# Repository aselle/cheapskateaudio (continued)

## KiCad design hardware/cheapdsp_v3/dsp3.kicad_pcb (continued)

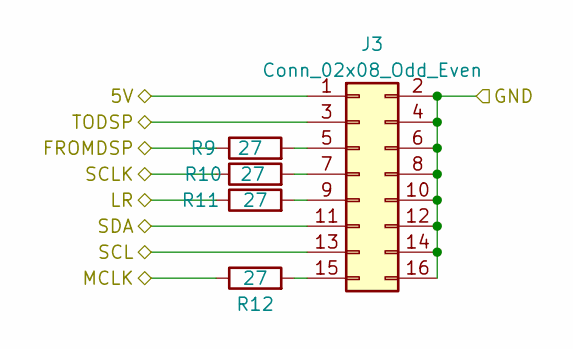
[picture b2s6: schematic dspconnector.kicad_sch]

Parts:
J3: Conn_02x08_Odd_Even; IDC-Header_2x08_P2.54mm_Vertical
R9, R10, R11, R12: 27; R_0603_1608Metric

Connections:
/DSP/I2S2_LR: R11.1; also elsewhere on the board
/DSP/I2S2_SCLK: R10.1; also elsewhere on the board
/DSP/I2S2_SDAT: R9.1; also elsewhere on the board
/DSP/MCLK2: R12.1; also elsewhere on the board
/DSP/SCL: J3.13; also elsewhere on the board
/DSP/SDA: J3.11; also elsewhere on the board
/DSP/dspconnector2/TODSP: J3.3
/RAW_5V: J3.1; also elsewhere on the board
GND: J3.2, J3.4, J3.6, J3.8, J3.10, J3.12, J3.14, J3.16; also elsewhere on the board
unnamed: J3.5, R9.2
unnamed: J3.7, R10.2
unnamed: J3.9, R11.2
unnamed: J3.15, R12.2

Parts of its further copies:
J1, J2, J4: Conn_02x08_Odd_Even; IDC-Header_2x08_P2.54mm_Vertical
R1, R2, R3, R4, R5, R6, R7, R8, R13, R14, R15, R16: 27; R_0603_1608Metric

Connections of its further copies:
/DSP/I2S0_LR: R3.1; also elsewhere on the board
/DSP/I2S0_SCLK: R2.1; also elsewhere on the board
/DSP/I2S0_SDAT: R1.1; also elsewhere on the board
/DSP/I2S1_LR: R7.1; also elsewhere on the board
/DSP/I2S1_SCLK: R6.1; also elsewhere on the board
/DSP/I2S1_SDAT: R5.1; also elsewhere on the board
/DSP/I2S3_LR: R15.1; also elsewhere on the board
/DSP/I2S3_SCLK: R14.1; also elsewhere on the board
/DSP/I2S3_SDAT: R13.1; also elsewhere on the board
/DSP/MCLK0: R4.1; also elsewhere on the board
/DSP/MCLK1: R8.1; also elsewhere on the board
/DSP/MCLK3: R16.1; also elsewhere on the board
/DSP/SCL: J1.13, J2.13, J4.13; also elsewhere on the board
/DSP/SDA: J1.11, J2.11, J4.11; also elsewhere on the board
/DSP/dspconnector1/TODSP: J2.3
/DSP/dspconnector3/TODSP: J4.3
/DSP/dspconnector/TODSP: J1.3
/RAW_5V: J1.1, J2.1, J4.1; also elsewhere on the board
GND: J1.2, J1.4, J1.6, J1.8, J1.10, J1.12, J1.14, J1.16, J2.2, J2.4, J2.6, J2.8, J2.10, J2.12, J2.14, J2.16, J4.2, J4.4, J4.6, J4.8, J4.10, J4.12, J4.14, J4.16; also elsewhere on the board
unnamed: J1.5, R1.2
unnamed: J1.7, R2.2
unnamed: J1.9, R3.2
unnamed: J1.15, R4.2
unnamed: J2.5, R5.2
unnamed: J2.7, R6.2
unnamed: J2.9, R7.2
unnamed: J2.15, R8.2
unnamed: J4.5, R13.2
unnamed: J4.7, R14.2
unnamed: J4.9, R15.2
unnamed: J4.15, R16.2

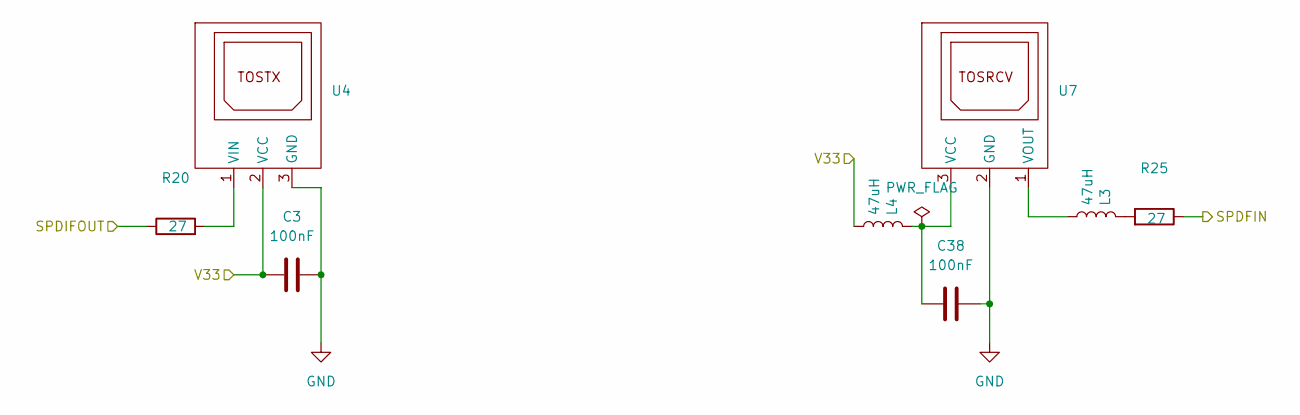
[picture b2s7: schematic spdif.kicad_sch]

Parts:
C3, C38: 100nF; C_0603_1608Metric
L3, L4: 47uH; L_0603_1608Metric
R20, R25: 27; R_0603_1608Metric
U4: PLT133-T10
U7: PLR135-T8

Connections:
/DSP/SPDIFIN: R25.1; also elsewhere on the board
/DSP/SPDIFOUT: R20.1; also elsewhere on the board
GND: C3.2, C38.1, U4.3 (GND), U7.2 (GND); also elsewhere on the board
unnamed: L3.1, R25.2
unnamed: R20.2, U4.1 (VIN)
unnamed: C38.2, L4.1, U7.3 (VCC)
unnamed: L3.2, U7.1 (VOUT)
V33: C3.1, L4.2, U4.2 (VCC); also elsewhere on the board

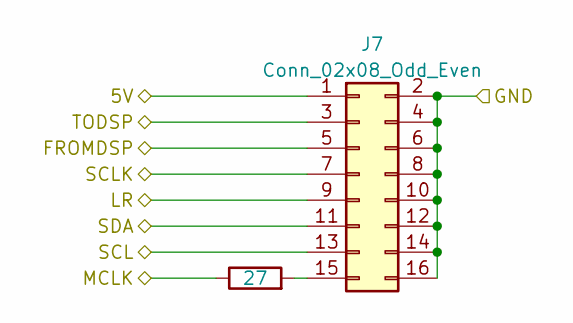
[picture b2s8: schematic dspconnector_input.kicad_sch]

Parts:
J7: Conn_02x08_Odd_Even; IDC-Header_2x08_P2.54mm_Vertical
R26: 27; R_0603_1608Metric

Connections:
/DSP/I2SIN0_LR: J7.9; also elsewhere on the board
/DSP/I2SIN0_SCLK: J7.7; also elsewhere on the board
/DSP/I2SIN0_SDAT: J7.3; also elsewhere on the board
/DSP/MCLK4: R26.1; also elsewhere on the board
/DSP/SCL: J7.13; also elsewhere on the board
/DSP/SDA: J7.11; also elsewhere on the board
/DSP/dspconnector_input/FROMDSP: J7.5
/RAW_5V: J7.1; also elsewhere on the board
GND: J7.2, J7.4, J7.6, J7.8, J7.10, J7.12, J7.14, J7.16; also elsewhere on the board
unnamed: J7.15, R26.2

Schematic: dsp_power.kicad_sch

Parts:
C2, C25: 10uF; CP_Elec_4x4.5
C5, C8, C11, C14: 10nF; C_0603_1608Metric
C6, C7, C9, C12, C15, C17, C18, C19, C20, C22, C29: 100nF; C_0603_1608Metric
C10, C31, C51: 10uF; C_0603_1608Metric
C21: 1uF; C_0603_1608Metric
C26, C27: 22uF; CP_Elec_4x4.5
C28: 22uF; C_0603_1608Metric
D2: LED; LED_0805_2012Metric_Pad1.15x1.40mm_HandSolder
FB2, FB3: 600R @ 100Mhz; R_0805_2012Metric
R31: 4.7k; R_0603_1608Metric
R42: .5; R_0603_1608Metric
U5: LD1117S33TR_SOT223; SOT-223-3_TabPin2

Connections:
/DSP/AVDD: C21.1, C22.1, FB3.2; also elsewhere on the board
/DSP/DVDD: C5.1, C6.1, C8.1, C9.1, C11.1, C12.1, C14.1, C15.1, R42.1; also elsewhere on the board
/DSP/dsp_power/V33_BEFORE_F: C28.1, C29.1, D2.2 (A), FB2.1, U5.2 (VO)
/RAW_5V: C25.1, C26.1, C27.1, U5.3 (VI); also elsewhere on the board
GND: C2.2, C5.2, C6.2, C7.2, C8.2, C9.2, C10.2, C11.2, C12.2, C14.2, C15.2, C17.2, C18.2, C19.2, C20.2, C21.2, C22.2, C25.2, C26.2, C27.2, C28.2, C29.2, C31.2, C51.2, R31.2, U5.1 (GND); also elsewhere on the board
unnamed: C31.1, R42.2
unnamed: D2.1 (K), R31.1
V33: C2.1, C7.1, C10.1, C17.1, C18.1, C19.1, C20.1, C51.1, FB2.2, FB3.1; also elsewhere on the board

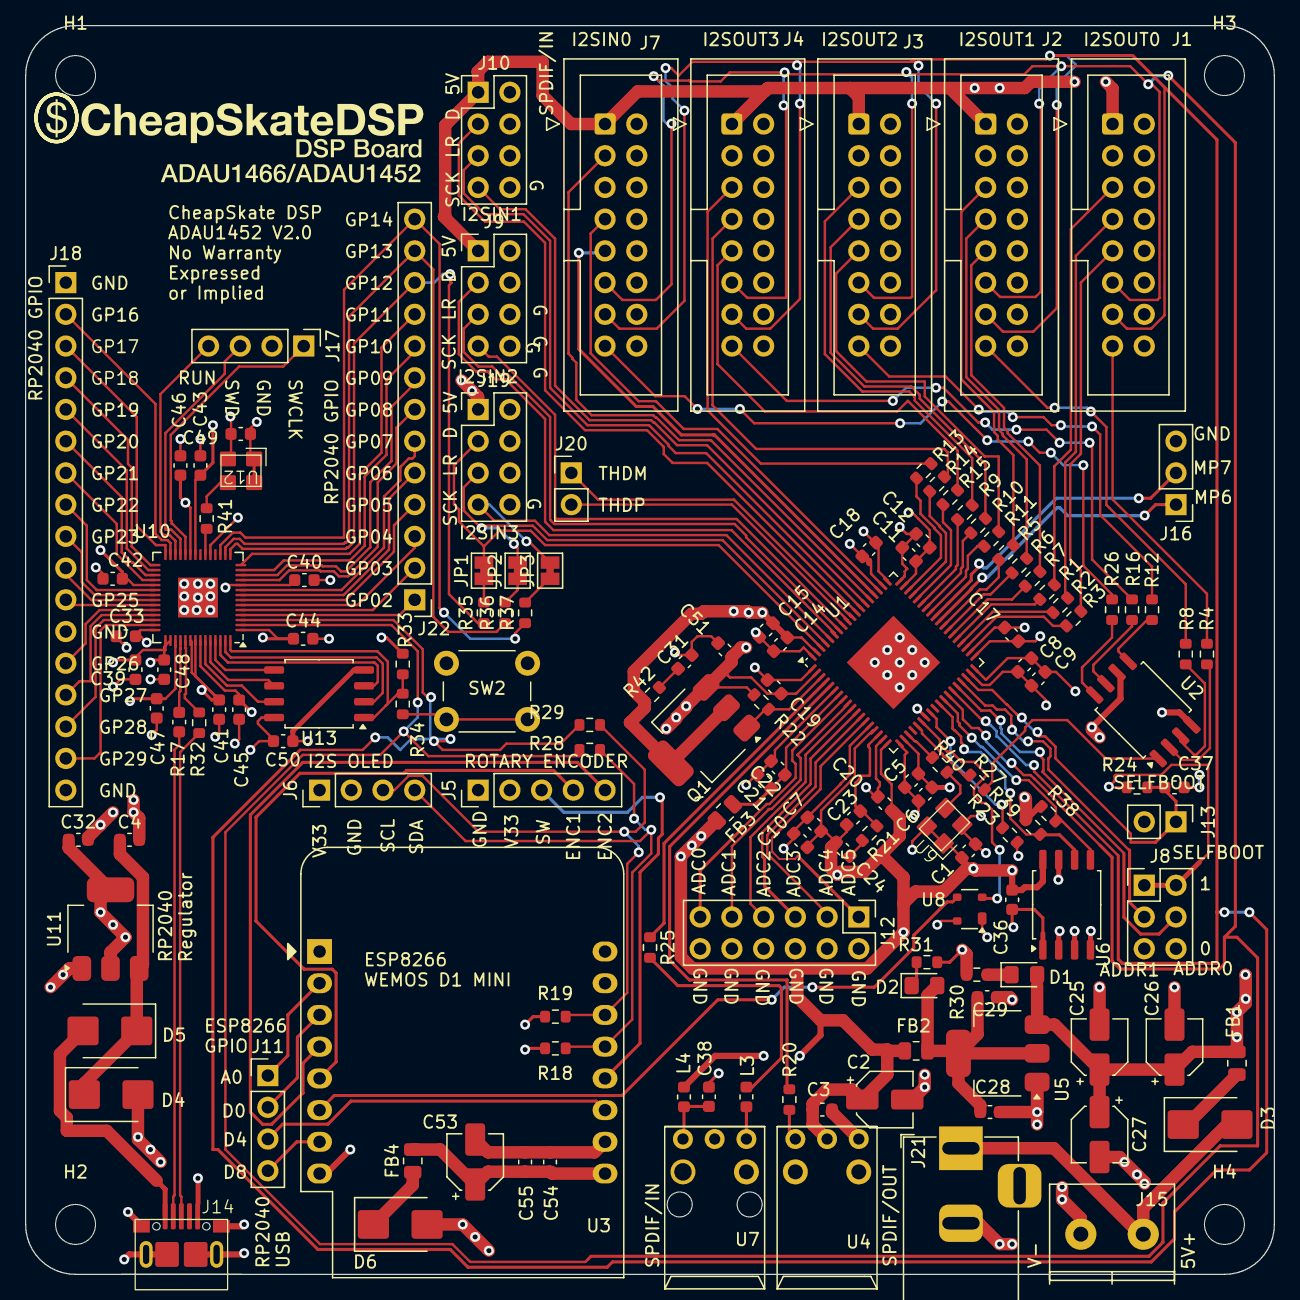
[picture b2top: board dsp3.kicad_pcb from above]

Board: 4 copper layers, 100.0 x 100.0 mm, 147 parts (0 on the bottom side), 152 nets.

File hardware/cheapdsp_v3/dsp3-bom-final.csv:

"Id";"Designator";"Footprint";"Quantity";"Designation";"Supplier and ref";
1;"R16,R12,R26,R10,R14,R2,R3,R27,R37,R35,R4,R7,R32,R25,R6,R36,R5,R11,R9,R1,R13,R20,R8,R15";"R_0603_1608Metric";24;"27";;;
2;"R24,R23";"R_0603_1608Metric";2;"10k";;;
3;"U8";"SOT-143";1;"UM811TE";;;
4;"C49,C3,C15,C36,C38,C20,C44,C46,C17,C30,C33,C40,C41,C45,C1,C42,C29,C9,C12,C6,C39,C50,C43,C34,C18,C22,C19";"C_0603_1608Metric";27;"100nF";;;
5;"TP3,TP1,TP2,TP4";"TestPoint_Pad_D1.0mm";4;"TestPoint";;;
6;"U7";"PLR135-T8";1;"~";;;
7;"J5";"PinHeader_1x05_P2.54mm_Vertical";1;"Conn_01x05";;;
8;"C37,C5,C14,C8,C11";"C_0603_1608Metric";5;"10nF";;;
9;"C35,C2,C25";"CP_Elec_4x4.5";3;"10uF";;;
10;"R18,R30,R19,R31";"R_0603_1608Metric";4;"4.7k";;;
11;"L4,L3";"L_0603_1608Metric";2;"47uH";;;
12;"U2";"SOIC-8_5.23x5.23mm_P1.27mm";1;"2305NZ";;;
13;"J17";"PinHeader_1x04_P2.54mm_Vertical";1;"Conn_01x04_Pin";;;
14;"J3,J1,J2,J7,J4";"IDC-Header_2x08_P2.54mm_Vertical";5;"Conn_02x08_Odd_Even";;;
15;"U9";"YSO110TR_SMD3225";1;"~";;;
16;"C23";"C_0603_1608Metric";1;"150pF";;;
17;"J13";"PinHeader_1x02_P2.54mm_Vertical";1;"Conn_01x02_Pin";;;
18;"R33";"R_0603_1608Metric";1;"DNF";;;
19;"J18";"IDC-Header_2x10_P2.54mm_Vertical";1;"Conn_02x10_Odd_Even";;;
20;"C48,C21,C47,C10,C16,C13,C7";"C_0603_1608Metric";7;"1uF";;;
21;"U3";"WEMOS_D1_mini_light";1;"WeMos_D1_mini";;;
22;"C27,C26";"CP_Elec_4x4.5";2;"22uF";;;
23;"D3,D4,D5,D6";"D_SMB";4;"D_Schottky";;;
24;"U12";"YSO110TR_SMD3225";1;"12MHz";;;
25;"U1";"LFCSP-72-1EP_10x10mm_P0.5mm_EP5.3x5.3mm";1;"ADAU1452";;;
26;"C24";"C_0603_1608Metric";1;"5.6nF";;;
27;"C28";"C_0603_1608Metric";1;"22uF";;;
28;"U13";"SOIC-8_5.23x5.23mm_P1.27mm";1;"W25Q128JVS";;;
29;"Q1";"SOT-223-3_TabPin2";1;"Q_PNP_BCE";;;
30;"U4";"PLT133-T10";1;"~";;;
31;"R28,R29";"R_0603_1608Metric";2;"0";;;
32;"FB1";"R_0805_2012Metric";1;"600 @ 100Mhz (2A)";;;
33;"J6,J11";"PinHeader_1x04_P2.54mm_Vertical";2;"Conn_01x04";;;
34;"C32,C4";"C_0603_1608Metric";2;"10uF";;;
35;"R34,R22";"R_0603_1608Metric";2;"1k";;;
36;"J12";"PinHeader_2x06_P2.54mm_Vertical";1;"Conn_02x06_Odd_Even";;;
37;"R38,R39";"R_0603_1608Metric";2;"2k";;;
38;"U5,U11";"SOT-223-3_TabPin2";2;"LD1117S33TR_SOT223";;;
39;"J14";"USB_Micro-B_Molex_47346-0001";1;"USB_B_Micro";;;
40;"R17";"C_0603_1608Metric";1;"27";;;
41;"J15";"KF301-5.0-2P";1;"Screw_Terminal_01x02";;;
42;"SW2";"SW_PUSH_6mm";1;"SW_SPST";;;
43;"D1,D2";"LED_0805_2012Metric_Pad1.15x1.40mm_HandSolder";2;"LED";;;
44;"J10,J9";"PinHeader_2x04_P2.54mm_Vertical";2;"Conn_02x04_Odd_Even";;;
45;"U10";"QFN-56-1EP_7x7mm_P0.4mm_EP3.2x3.2mm";1;"RP2040";;;
46;"R21";"R_0603_1608Metric";1;"4.3k";;;
47;"J8";"PinHeader_2x03_P2.54mm_Vertical";1;"Conn_02x03_Odd_Even";;;
48;"U6";"SOIC-8_5.23x5.23mm_P1.27mm";1;"24LC32";;;
49;"FB3,FB2";"R_0805_2012Metric";2;"600R @ 100Mhz";;;
50;"J16";"PinHeader_1x05_P2.54mm_Vertical";1;"Conn_01x05_Pin";;;

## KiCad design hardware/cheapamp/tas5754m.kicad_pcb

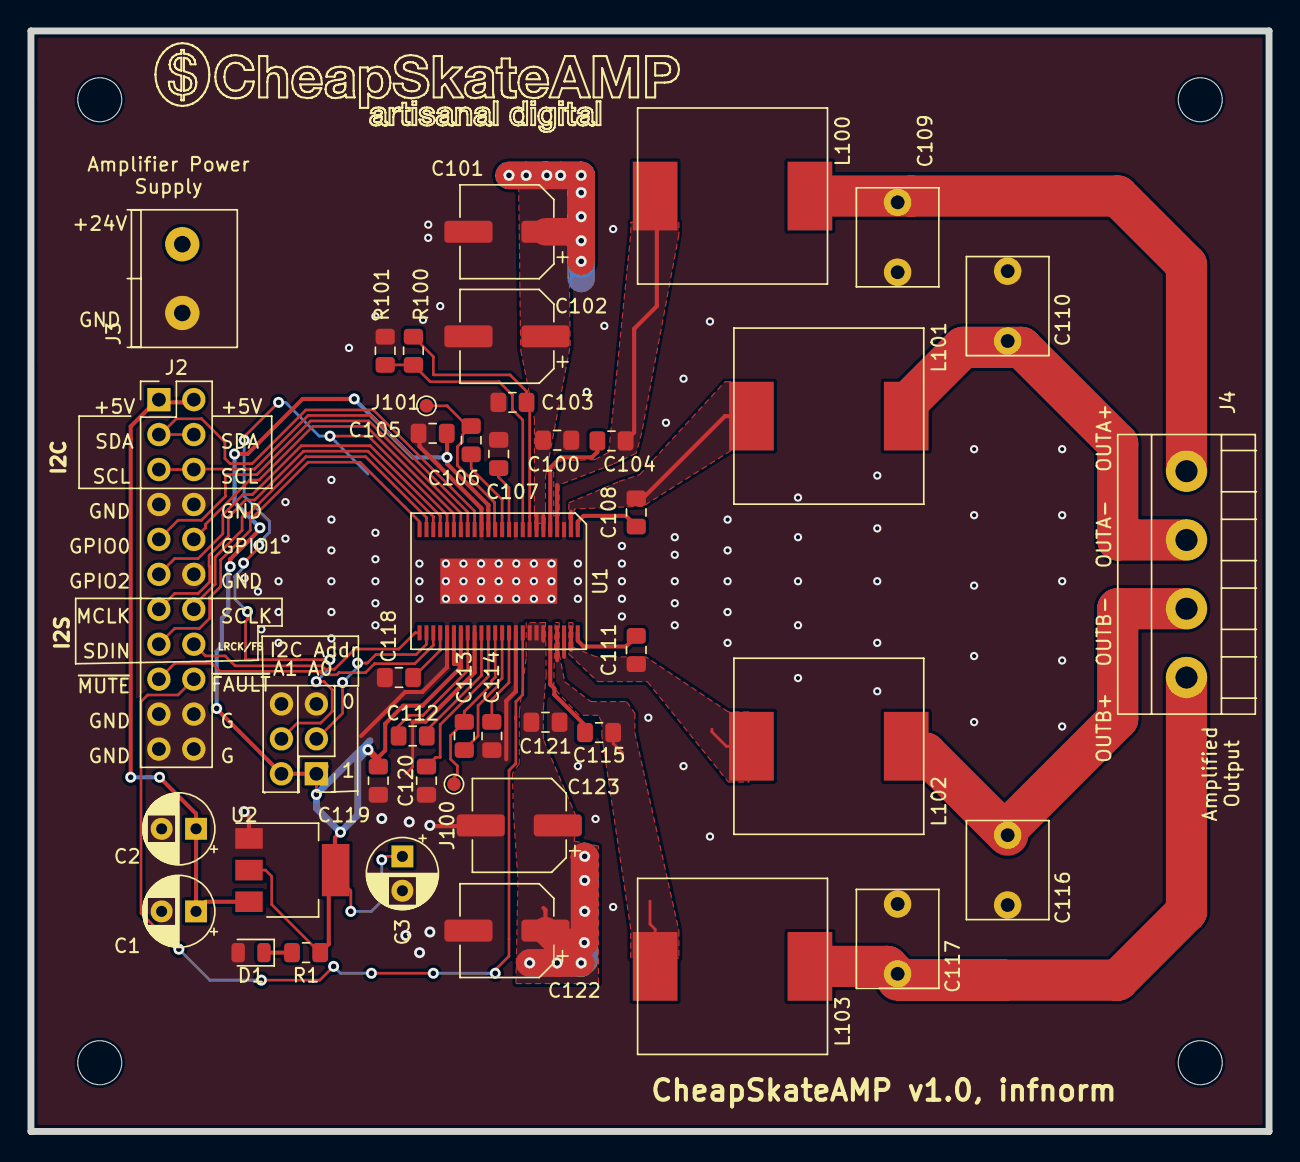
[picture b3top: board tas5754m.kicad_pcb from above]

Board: 2 copper layers, 90.0 x 80.0 mm, 43 parts (0 on the bottom side), 42 nets.

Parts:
C1: 0.1uF; CP_Radial_D5.0mm_P2.50mm
C2: 47uF; CP_Radial_D5.0mm_P2.50mm
C3: 10uF; CP_Radial_D5.0mm_P2.50mm
C100, C121: 0.1uF; C_0805_2012Metric_Pad1.15x1.40mm_HandSolder
C101, C102, C122, C123: 22uF; CP_Elec_6.3x5.4
C103, C105, C112, C118, C119, C120: 1uF; C_0805_2012Metric_Pad1.15x1.40mm_HandSolder
C104, C108, C111, C115: 0.22uF; C_0805_2012Metric_Pad1.15x1.40mm_HandSolder
C106, C107, C113, C114: 2.2uF; C_0805_2012Metric_Pad1.15x1.40mm_HandSolder
C109, C110, C116, C117: 1uF; CAP_PE105J2A0501
D1: LED; LED_0805_2012Metric
J1: Conn_02x03_Odd_Even; PinHeader_2x03_P2.54mm_Vertical
J2: Conn_02x11_Odd_Even; PinHeader_2x11_P2.54mm_Vertical
J3: Conn_01x02; KF301-5.0-2P
J4: Conn_01x04; DINKLE-EK508V-04P
J100, J101: TestPoint; TestPoint_Pad_D1.0mm
L100, L101, L102, L103: 10uH; inductor_ms1350
R1: 300; C_0805_2012Metric_Pad1.15x1.40mm_HandSolder
R100: 750k; C_0805_2012Metric_Pad1.15x1.40mm_HandSolder
R101: 150k; C_0805_2012Metric_Pad1.15x1.40mm_HandSolder
U1: TAS5754M; TSSOP48-TAS5574M
U2: AP1117-15; SOT-223-3_TabPin2

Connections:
ADDR0: J1.3, U1.26
ADDR1: J1.4, U1.20
BSTRPA+: C104.2, U1.5
BSTRPA-: C108.2, U1.1
BSTRPB+: C115.2, U1.44
BSTRPB-: C111.2, U1.48
CN: C112.2, U1.34
CP: C112.1, U1.32
CPVSS: C120.1, U1.35
DAC_OUTA: C106.1, J101.1, U1.13
DAC_OUTB: C113.1, J100.1, U1.36
DVDD_REG: C118.1, U1.28
GND: C1.2, C2.2, C3.2, C100.2, C101.2, C102.2, C103.2, C105.2, C107.2, C109.2, C110.2, C114.2, C116.2, C117.2, C118.2, C119.2, C120.2, C121.2, C122.2, C123.2, D1.2, J1.5, J1.6, J2.7, J2.8, J2.12, J2.19, J2.20, J2.21, J2.22, J3.2, R100.1, U1.3, U1.10, U1.15, U1.29, U1.33, U1.39, U1.46, U1.PAD, U2.1
GPIO0: J2.9, U1.18
GPIO1: J2.10, U1.19
GPIO2: J2.11, U1.21
GVDO: C103.1, R101.2, U1.8
LRCK/FS: J2.16, U1.25
MCLK: J2.13, U1.22
unnamed: D1.1, R1.2
OUTA+: C109.1, J4.1, L100.2
OUTA-: C110.1, J4.2, L101.2
OUTB+: C117.1, J4.4, L103.2
OUTB-: C116.1, J4.3, L102.2
PVDD: C100.1, C101.1, C102.1, C121.1, C122.1, C123.1, J3.1, U1.6, U1.7, U1.41, U1.42, U1.43
RAW5V: C1.1, C2.1, J2.1, J2.2, U2.3
SCL: J2.5, J2.6, U1.17
SCLK: J2.14, U1.23
SDA: J2.3, J2.4, U1.16
SDIN: J2.15, U1.24
SPK_GAIN/FREQ: R100.2, R101.1, U1.9
SPK_INA+: C106.2, U1.12
SPK_INA-: C107.1, U1.11
SPK_INB+: C113.2, U1.37
SPK_INB-: C114.1, U1.38
SPK_OUTA+: C104.1, L100.1, U1.4
SPK_OUTA-: C108.1, L101.1, U1.2
SPK_OUTB+: C115.1, L103.1, U1.45
SPK_OUTB-: C111.1, L102.1, U1.47
V33: C3.1, C105.1, C119.1, J1.1, J1.2, R1.1, U1.14, U1.30, U1.31, U2.2
~SPK_FAULT: J2.18, U1.40
~SPK_MUTE: J2.17, U1.27

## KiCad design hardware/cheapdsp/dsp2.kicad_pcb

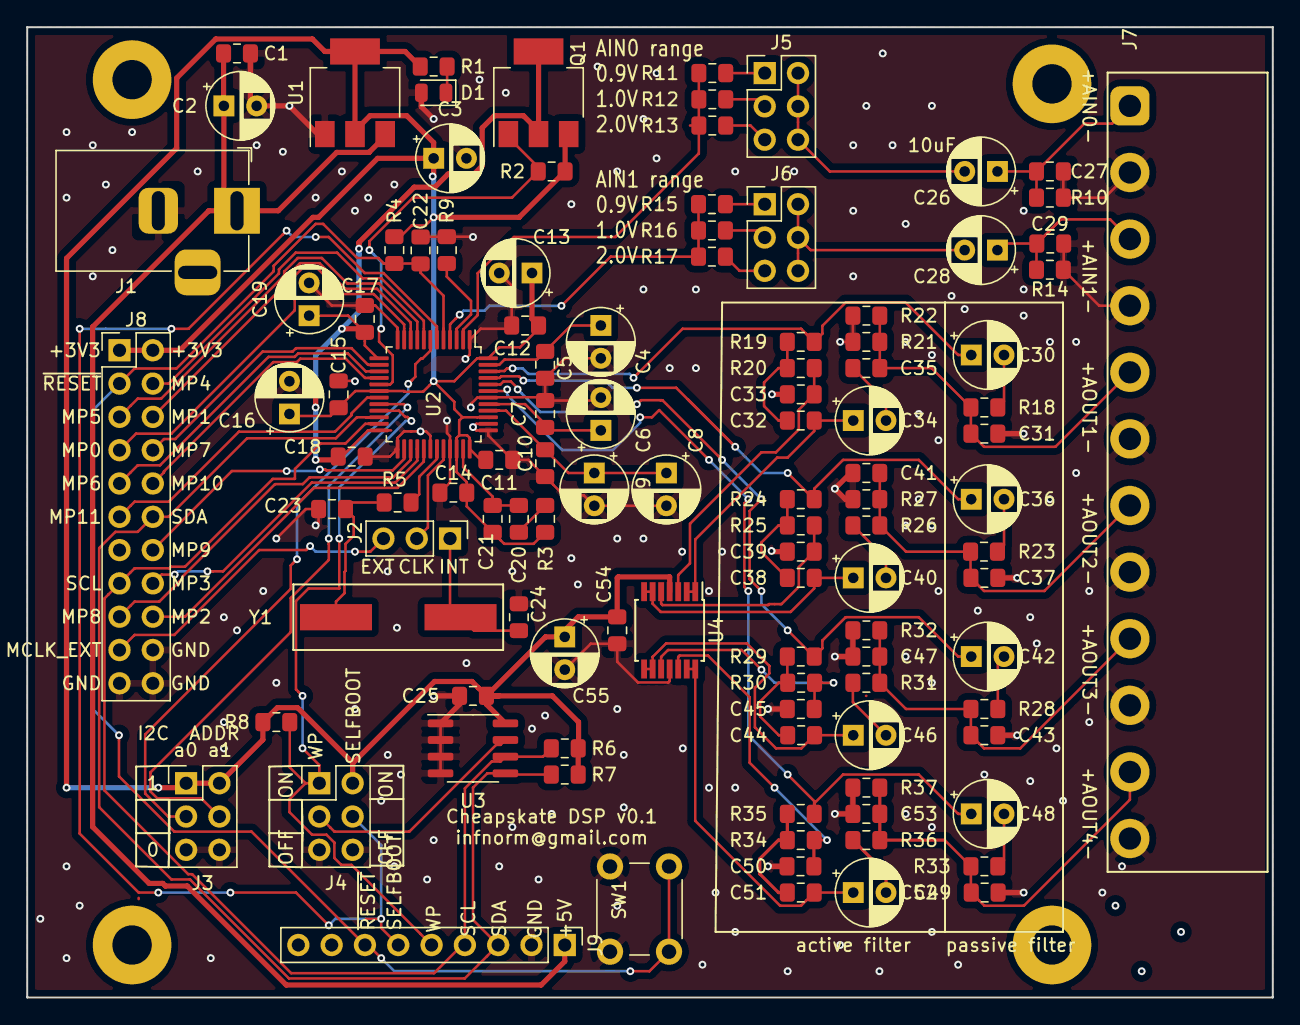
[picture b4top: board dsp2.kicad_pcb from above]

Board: 2 copper layers, 95.0 x 74.0 mm, 113 parts (0 on the bottom side), 77 nets.

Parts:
C1, C5, C7, C10, C11, C12, C14, C15, C17, C18, C22, C25, C54: 100nF; C_0805_2012Metric_Pad1.15x1.40mm_HandSolder
C2, C8, C30, C36, C42, C48: 47uF; CP_Radial_D5.0mm_P2.50mm
C3, C4, C6, C9, C13, C16, C19, C26, C28, C34, C40, C46, C52, C55: 10uF; CP_Radial_D5.0mm_P2.50mm
C20: 56nF; C_0805_2012Metric_Pad1.15x1.40mm_HandSolder
C21, C35, C41, C47, C53: 3.3nF; C_0805_2012Metric_Pad1.15x1.40mm_HandSolder
C23, C24: 22pF; C_0805_2012Metric_Pad1.15x1.40mm_HandSolder
C27, C29: 100pF; C_0805_2012Metric_Pad1.15x1.40mm_HandSolder
C31, C37, C43, C49: 5.6nF; C_0805_2012Metric_Pad1.15x1.40mm_HandSolder
C32, C38, C44, C50: 470pF; C_0805_2012Metric_Pad1.15x1.40mm_HandSolder
C33, C39, C45, C51: 150pF; C_0805_2012Metric_Pad1.15x1.40mm_HandSolder
D1: LED; LED_0805_2012Metric
J1: Barrel_Jack; BarrelJack_Horizontal
J2: Conn_01x03; PinHeader_1x03_P2.54mm_Vertical
J3, J4, J5, J6: Conn_02x03_Odd_Even; PinHeader_2x03_P2.54mm_Vertical
J7: Screw_Terminal_01x12; Ningbo-Kangnex-Elec-WJ2EDGR-5-08-12P
J8: Conn_02x11_Odd_Even; PinHeader_2x11_P2.54mm_Vertical
J9: Conn_01x09; PinHeader_1x09_P2.54mm_Vertical
PAD1, PAD1#2, PAD1#3, PAD1#4: MountingHole_3mm_Pad
Q1: Q_PNP_BCE; SOT-223-3_TabPin2
R1: 300; R_0805_2012Metric_Pad1.15x1.40mm_HandSolder
R2: 1k; R_0805_2012Metric_Pad1.15x1.40mm_HandSolder
R3: 465; R_0805_2012Metric_Pad1.15x1.40mm_HandSolder
R4, R6, R7, R8: 10k; R_0805_2012Metric_Pad1.15x1.40mm_HandSolder
R5: 100; R_0805_2012Metric_Pad1.15x1.40mm_HandSolder
R9, R13, R17: 18k; R_0805_2012Metric_Pad1.15x1.40mm_HandSolder
R10, R14, R22, R27, R32, R37: 49.9k; R_0805_2012Metric_Pad1.15x1.40mm_HandSolder
R11, R15: 7k; R_0805_2012Metric_Pad1.15x1.40mm_HandSolder
R12, R16: 8k; R_0805_2012Metric_Pad1.15x1.40mm_HandSolder
R18, R23, R28, R33: 560; R_0805_2012Metric_Pad1.15x1.40mm_HandSolder
R19, R20, R24, R25, R29, R30, R34, R35: 4.75k; R_0805_2012Metric_Pad1.15x1.40mm_HandSolder
R21, R26, R31, R36: 604; R_0805_2012Metric_Pad1.15x1.40mm_HandSolder
SW1: SW_Push; SW_PUSH_6mm
U1: AP1117-15; SOT-223-3_TabPin2
U2: ADAU1701; LQFP-48_7x7mm_P0.5mm
U3: 24LC16; SOIC-8_3.9x4.9mm_P1.27mm
U4: Opamp_Quad_Generic; TSSOP-14_4.4x5mm_P0.65mm
Y1: Crystal; HC-49SMD-aselle

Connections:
+3V3: C3.1, C11.1, C12.1, C13.1, C14.1, C15.1, C16.1, C21.1, C25.1, C54.1, C55.1, J3.1, J3.2, J4.2, J8.1, J8.2, Q1.3, R1.1, R2.1, R3.1, R4.1, R6.1, R7.1, R8.1, U1.2, U2.18, U2.34, U2.36, U2.39, U2.48, U3.8, U4.4
ADC0: R11.2, R12.2, R13.2, U2.2
ADC1: R15.2, R16.2, R17.2, U2.4
ADDR0: J3.3, U2.7
ADDR1: J3.4, U2.20
AIN0: C26.1, C27.1, J7.1, R10.1
AIN1: C28.1, C29.1, J7.3, R14.1
DVDD: C17.1, C18.1, C19.1, Q1.2, U2.13, U2.24
FILTER_VOUT0: C31.1, C35.1, J7.5, R18.2, R21.2, R22.1
FILTER_VOUT1: C37.1, C41.1, J7.7, R23.2, R26.2, R27.1
FILTER_VOUT2: C43.1, C47.1, J7.9, R28.2, R31.2, R32.1
FILTER_VOUT3: C49.1, C53.1, J7.11, R33.2, R36.2, R37.1
GND: C1.2, C2.2, C3.2, C4.2, C5.2, C6.2, C7.2, C8.2, C9.2, C10.2, C11.2, C12.2, C13.2, C14.2, C15.2, C16.2, C17.2, C18.2, C19.2, C22.2, C23.2, C24.2, C25.2, C27.2, C29.2, C31.2, C33.2, C35.2, C37.2, C39.2, C41.2, C43.2, C45.2, C47.2, C49.2, C51.2, C53.2, C54.2, C55.2, D1.2, J1.2, J3.5, J3.6, J4.5, J4.6, J7.2, J7.4, J7.6, J7.8, J7.10, J7.12, J8.20, J8.21, J8.22, J9.2, R9.2, R10.2, R14.2, R22.2, R27.2, R32.2, R37.2, SW1.2, U1.1, U2.1, U2.12, U2.25, U2.30, U2.33, U2.37, U2.38, U2.42, U3.1, U3.2, U3.3, U3.4, U4.11
MCLK_CHOSEN: J2.2, U2.32
MCLK_EXT: J2.3, J8.19
MCLK_INT: C24.1, J2.1, Y1.2
MP0: J8.7, U2.11
MP1: J8.6, U2.10
MP2: J8.18, U2.29
MP3: J8.16, U2.28
MP4: J8.4, U2.8
MP5: J8.5, U2.9
MP6: J8.9, U2.15
MP7: J8.8, U2.14
MP8: J8.17, U2.27
MP9: J8.14, U2.26
MP10: J8.10, U2.16
MP11: J8.11, U2.19
unnamed: D1.1, R1.2
unnamed: C4.1, C5.1, U2.47
unnamed: C6.1, C7.1, U2.41
unnamed: C8.1, C9.1, C10.1, U2.40
unnamed: Q1.1, R2.2, U2.17
unnamed: C20.1, R3.2
unnamed: C20.2, C21.2, U2.35
unnamed: R5.1, U2.31
unnamed: C23.1, R5.2, Y1.1
unnamed: R9.1, U2.3
unnamed: J5.1, R11.1
unnamed: C26.2, J5.2, J5.4, J5.6
unnamed: J5.3, R12.1
unnamed: J5.5, R13.1
unnamed: J6.1, R15.1
unnamed: C28.2, J6.2, J6.4, J6.6
unnamed: J6.3, R16.1
unnamed: J6.5, R17.1
unnamed: C30.2, R18.1
unnamed: C32.1, R19.2, R20.1
unnamed: C33.1, R20.2, U4.3
unnamed: C32.2, C34.1, U4.1, U4.2
unnamed: C34.2, R21.1
unnamed: C36.2, R23.1
unnamed: C38.1, R24.2, R25.1
unnamed: C39.1, R25.2, U4.5
unnamed: C38.2, C40.1, U4.6, U4.7
unnamed: C40.2, R26.1
unnamed: C42.2, R28.1
unnamed: C44.1, R29.2, R30.1
unnamed: C45.1, R30.2, U4.10
unnamed: C44.2, C46.1, U4.8, U4.9
unnamed: C46.2, R31.1
unnamed: C48.2, R33.1
unnamed: C50.1, R34.2, R35.1
unnamed: C51.1, R35.2, U4.12
unnamed: C50.2, C52.1, U4.13, U4.14
unnamed: C52.2, R36.1
RAW_+5V: C1.1, C2.1, J1.1, J9.1, U1.3
SCL: J8.15, J9.4, R6.2, U2.23, U3.6
SDA: J8.12, J9.3, R7.2, U2.22, U3.5
SELFBOOT: J4.4, J9.6, U2.6
VOUT0: C30.1, R19.1, U2.46
VOUT1: C36.1, R24.1, U2.45
VOUT2: C42.1, R29.1, U2.44
VOUT3: C48.1, R34.1, U2.43
WP: J4.1, J9.5, R8.2, U2.21
WP_EEPROM: J4.3, U3.7
~RESET: C22.1, J8.3, J9.7, R4.2, SW1.1, U2.5
